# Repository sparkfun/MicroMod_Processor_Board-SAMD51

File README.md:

SparkFun MicroMod SAMD51 Processor
========================================

[*SparkFun MicroMod SAMD51 Processor (DEV-16791)*](https://www.sparkfun.com/products/16791)

With a 32-bit ARM Cortex-M4F MCU, the SparkFun MicroMod SAMD51 Processor Board is one powerful microcontroller packaged on a small board! The provides you with an economical and easy to use development platform if you're needing more power with minimal working space. This MicroMod SAMD51 even comes flashed with the same convenient UF2 bootloader like the SAMD51 Thing Plus and the RedBoard Turbo. The MicroMod SAMD51 uses the MicroMod Hardware pinout to easily switch between carrier boards.

The ATSAMD51J20 utilizes a 32-bit ARM Cortex-M4 processor with Floating Point Unit (FPU), running up to 120MHz, up to 1MB of flash memory, up to 256KB of SRAM with ECC, up to 6 SERCOM interfaces, and other features.

Repository Contents
-------------------

* **/Arduino Board Files** - Board definitions for MicroMod SAMD51
* **/Documentation** - Datasheets, additional product information
* **/Hardware** - Eagle design files (.brd, .sch)
* **/Production** - Production panel files (.brd)
* **/uf2-bootloader** - Default firmware

Documentation
--------------
* **[Graphical Datasheet](https://github.com/sparkfun/Graphical_Datasheets/tree/main/Datasheets/SAM51)** - Pinout of the SAMD51 Processor Board
* **[Installing Board Definitions in the Arduino IDE](https://learn.sparkfun.com/tutorials/installing-board-definitions-in-the-arduino-ide)** - Information about installing Arduino Board Files for Arduino
* **[Hookup Guide](https://learn.sparkfun.com/tutorials/micromod-samd51-processor-board-hookup-guide)** - Basic hookup guide

Product Versions
----------------
* [DEV-16791](https://www.sparkfun.com/products/16791)

Version History
---------------
* [v1.3](https://github.com/sparkfun/MicroMod_Processor_Board-SAMD51/tree/v1.3) - Minor update to swap SPI1 lines to the external flash
* [v1.2](https://github.com/sparkfun/MicroMod_Processor_Board-SAMD51/tree/v1.2) - Initial Release 

License Information
-------------------

This product is _**open source**_! 

Please review the LICENSE.md file for license information. 

If you have any questions or concerns on licensing, please contact technical support on our [SparkFun forums](https://forum.sparkfun.com/viewforum.php?f=152).

Distributed as-is; no warranty is given.

- Your friends at SparkFun.

_<COLLABORATION CREDIT>_

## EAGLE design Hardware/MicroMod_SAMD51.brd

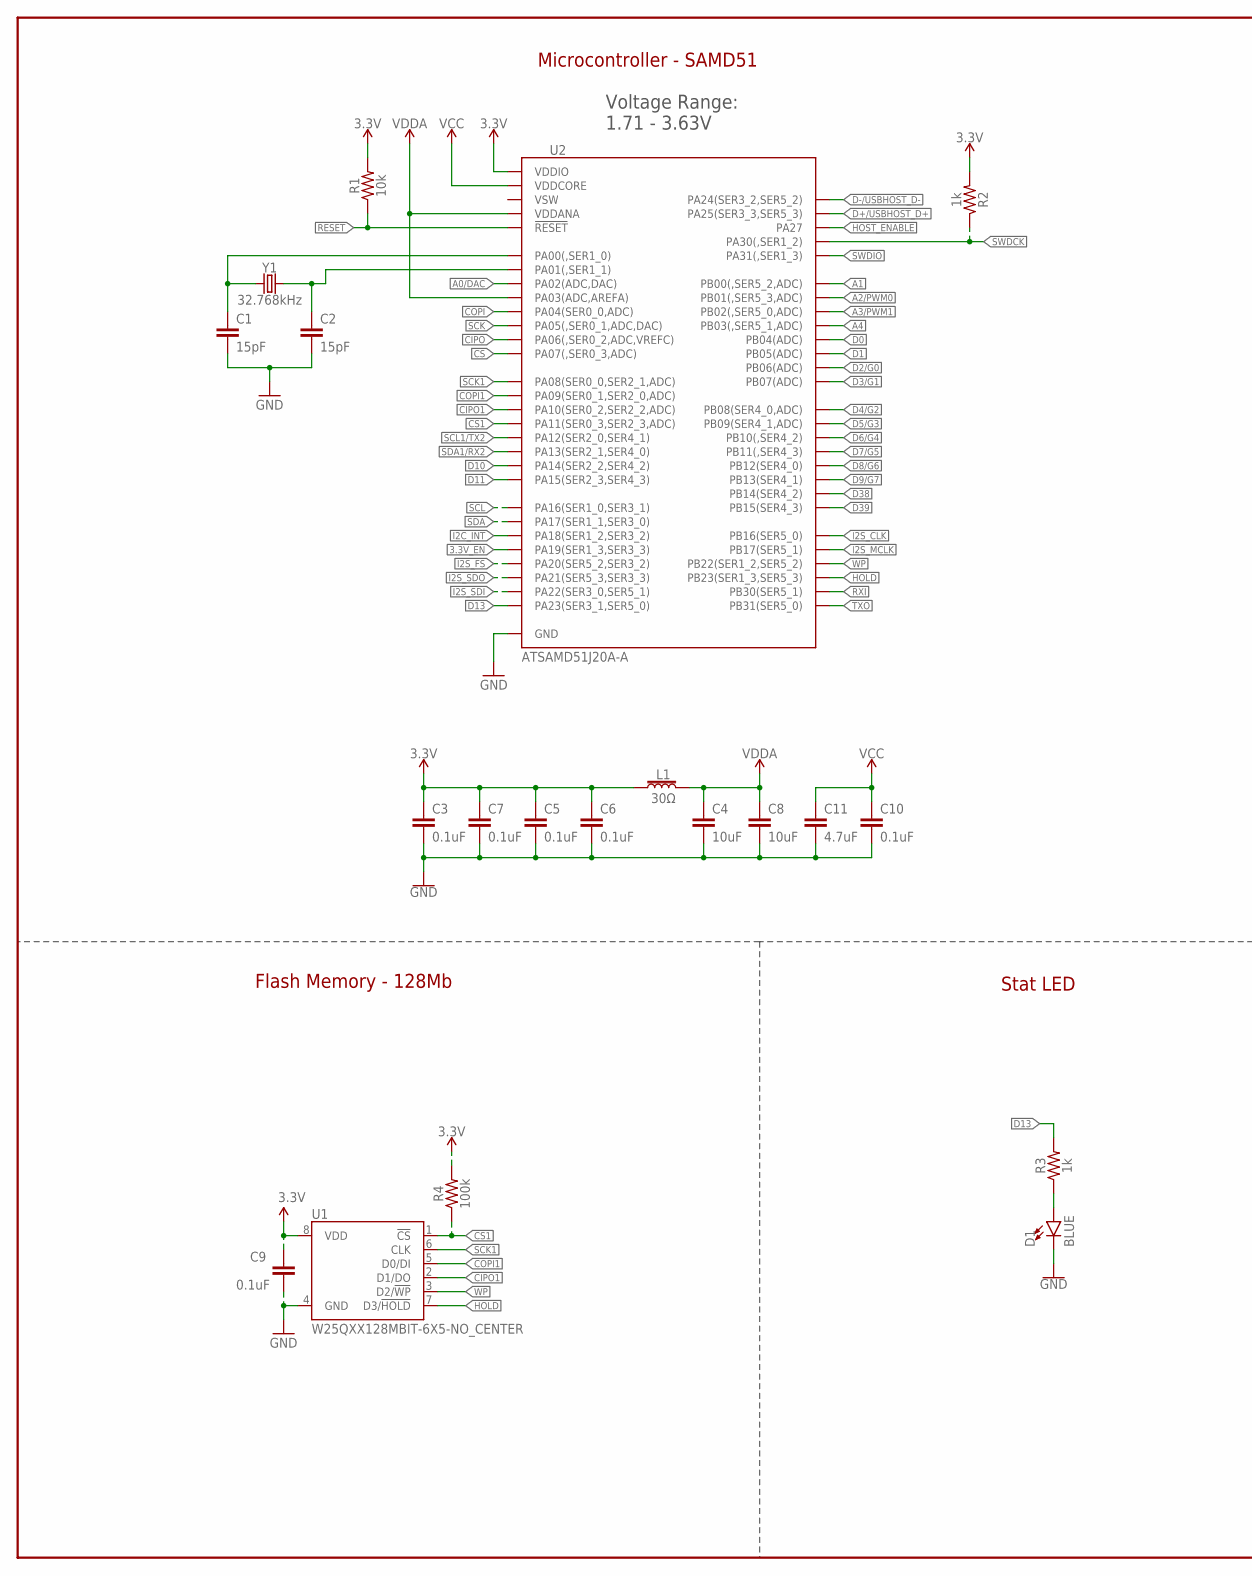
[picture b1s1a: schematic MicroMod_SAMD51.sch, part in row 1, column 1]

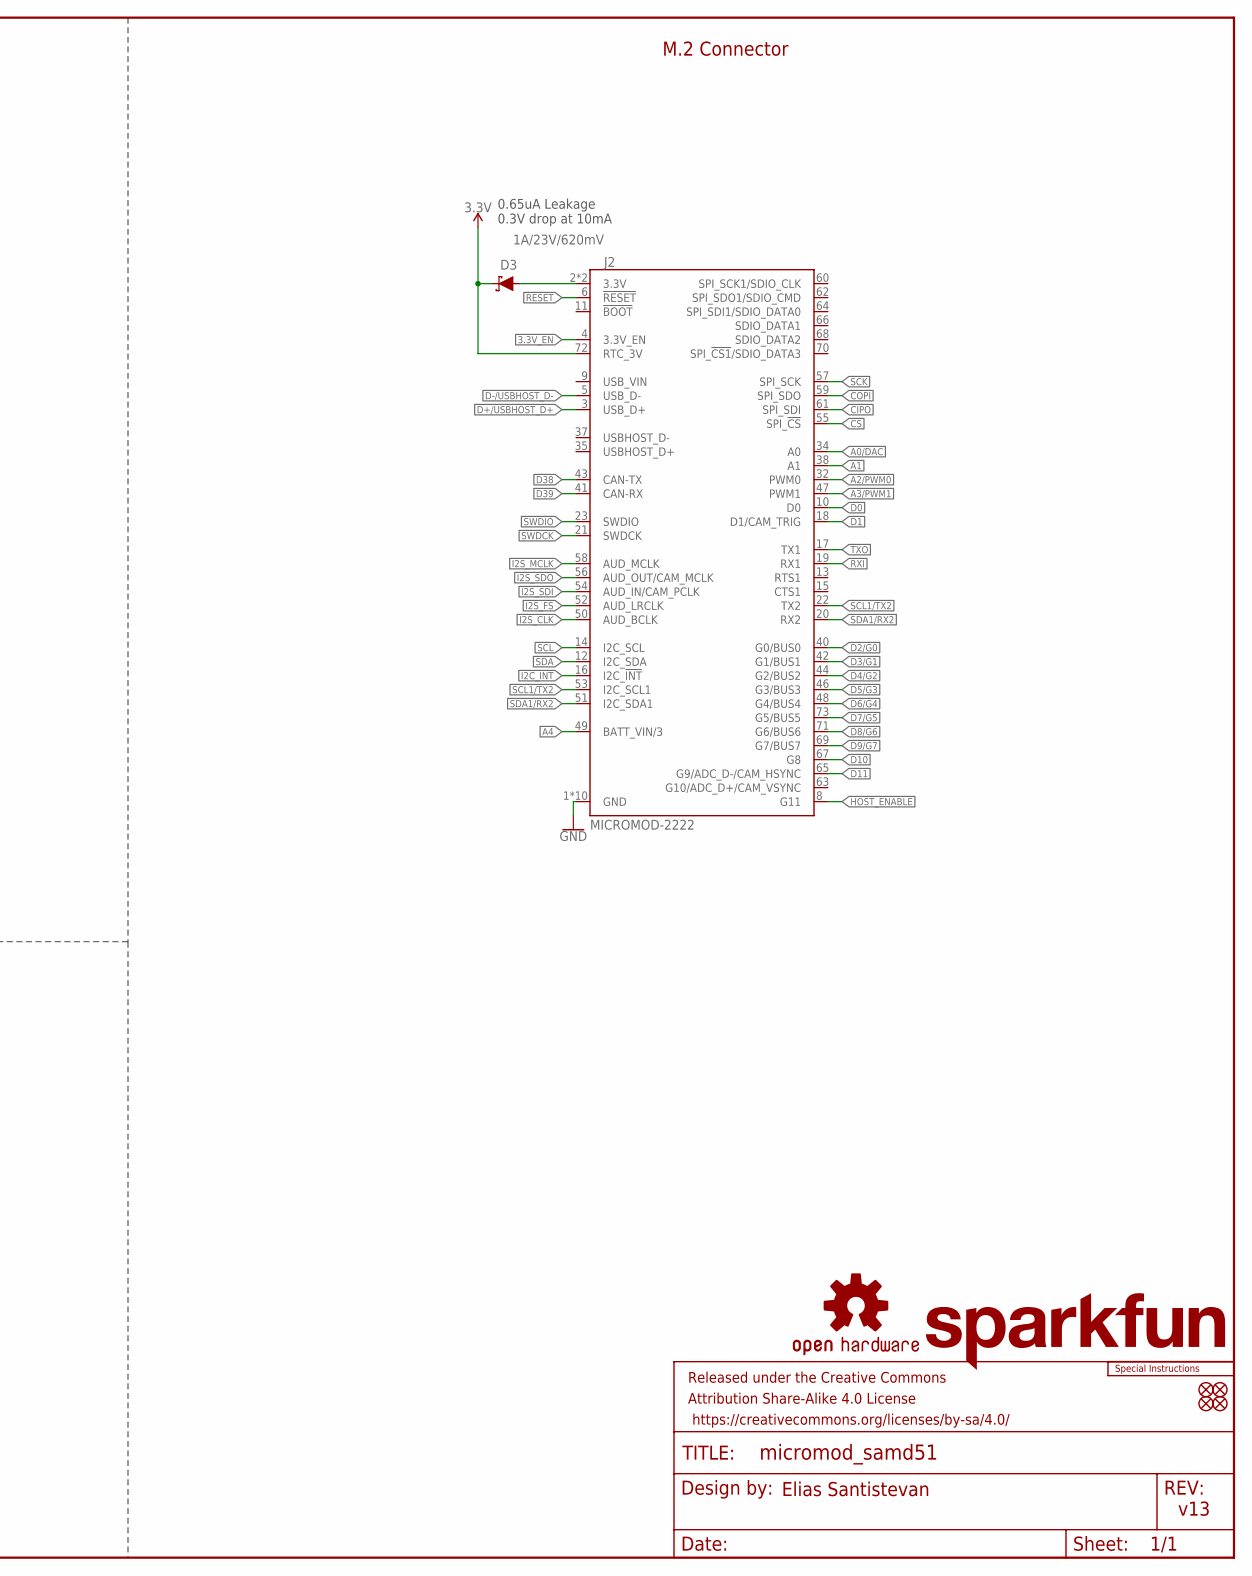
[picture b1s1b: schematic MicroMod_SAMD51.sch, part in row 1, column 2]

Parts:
C1, C2: 15pF; 0402-TIGHT
C3, C5, C6, C7, C9, C10: 0.1uF; 0402-TIGHT
C4, C8: 10uF; 0402-TIGHT
C11: 4.7uF; 0402-TIGHT
D1: BLUE; LED-0603
D3: 1A/23V/620mV; SOD-323
FD5, FD6, FD7, FD8: FIDUCIALUFIDUCIAL; FIDUCIAL-MICRO
FRAME2: FRAME-LEDGER; CREATIVE_COMMONS
J2: MICROMOD-2222; M.2-CARD-E-22
L1: 30Ω; 0402-TIGHT
LOGO2: OSHW-LOGOMINI; OSHW-LOGO-MINI
LOGO5: SPECIAL_INSTRUCTIONS-ORDERING; ORDERING_INSTRUCTIONS
LOGO6: SFE_LOGO_NAME.1_INCH; SFE_LOGO_NAME_.1
R1: 10k; 0402-TIGHT
R2, R3: 1k; 0402-TIGHT
R4: 100k; 0402-TIGHT
U1: W25QXX128MBIT-6X5-NO_CENTER; WSON-8-6X5-NO_CENTERPAD
U2: ATSAMD51J20A-A; TQFP64
Y1: 32.768kHz; CRYSTAL-SMD-3.2X1.5MM

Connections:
3.3V: C3.1, C5.1, C6.1, C7.1, C9.1, D3.C, J2.72 (RTC_3V), L1.1, R1.2, R2.2, R4.2, U1.8 (VDD), U2.21 (VDDIO), U2.34 (VDDIO), U2.48 (VDDIO), U2.56 (VDDIO)
3.3V_EN: J2.4 (3.3V_EN), U2.38 (PA19(SER1_3,SER3_3))
3.3V_IN: D3.A, J2.2 (3.3V), J2.74 (3.3V)
!CS: J2.55 (SPI_!CS!), U2.16 (PA07(,SER0_3,ADC))
!CS1!: R4.1, U1.1 (!CS!), U2.20 (PA11(SER0_3,SER2_3,ADC))
!HOLD!: U1.7 (D3/!HOLD!), U2.50 (PB23(SER1_3,SER5_3))
!RESET: J2.6 (!RESET!), R1.1, U2.52 (!RESET)
!WP!: U1.3 (D2/!WP!), U2.49 (PB22(SER1_2,SER5_2))
A0/DAC: J2.34 (A0), U2.3 (PA02(ADC,DAC))
A1: J2.38 (A1), U2.61 (PB00(,SER5_2,ADC))
A2/PWM0: J2.32 (PWM0), U2.62 (PB01(,SER5_3,ADC))
A3/PWM1: J2.47 (PWM1), U2.63 (PB02(,SER5_0,ADC))
A4: J2.49 (BATT_VIN/3), U2.64 (PB03(,SER5_1,ADC))
CIPO: J2.61 (SPI_SDI), U2.15 (PA06(,SER0_2,ADC,VREFC))
CIPO1: U1.2 (D1/DO), U2.19 (PA10(SER0_2,SER2_2,ADC))
COPI: J2.59 (SPI_SDO), U2.13 (PA04(SER0_0,ADC))
COPI1: U1.5 (D0/DI), U2.18 (PA09(SER0_1,SER2_0,ADC))
D0: J2.10 (D0), U2.5 (PB04(ADC))
D1: J2.18 (D1/CAM_TRIG), U2.6 (PB05(ADC))
D2/G0: J2.40 (G0/BUS0), U2.9 (PB06(ADC))
D3/G1: J2.42 (G1/BUS1), U2.10 (PB07(ADC))
D4/G2: J2.44 (G2/BUS2), U2.11 (PB08(SER4_0,ADC))
D5/G3: J2.46 (G3/BUS3), U2.12 (PB09(SER4_1,ADC))
D6/G4: J2.48 (G4/BUS4), U2.23 (PB10(,SER4_2))
D7/G5: J2.73 (G5/BUS5), U2.24 (PB11(,SER4_3))
D8/G6: J2.71 (G6/BUS6), U2.25 (PB12(SER4_0))
D9/G7: J2.69 (G7/BUS7), U2.26 (PB13(SER4_1))
D10: J2.67 (G8), U2.31 (PA14(SER2_2,SER4_2))
D11: J2.65 (G9/ADC_D-/CAM_HSYNC), U2.32 (PA15(SER2_3,SER4_3))
D13: R3.2, U2.44 (PA23(SER3_1,SER5_0))
D38: J2.43 (CAN-TX), U2.27 (PB14(SER4_2))
D39: J2.41 (CAN-RX), U2.28 (PB15(SER4_3))
D+/USBHOST_D+: J2.3 (USB_D+), U2.46 (PA25(SER3_3,SER5_3))
D-/USBHOST_D-: J2.5 (USB_D-), U2.45 (PA24(SER3_2,SER5_2))
GND: C1.2, C2.2, C3.2, C4.2, C5.2, C6.2, C7.2, C8.2, C9.2, C10.2, C11.2, D1.C, J2.1 (GND), J2.7 (GND), J2.33 (GND), J2.36 (GND), J2.39 (GND), J2.45 (GND), J2.75 (GND), J2.GND1 (GND), J2.GND2 (GND), J2.GND3 (GND), U1.4 (GND), U2.7 (GND), U2.22 (GND), U2.33 (GND), U2.47 (GND), U2.54 (GND)
HOST_ENABLE: J2.8 (G11), U2.51 (PA27)
I2C_!INT!: J2.16 (I2C_!INT!), U2.37 (PA18(SER1_2,SER3_2))
I2S_CLK: J2.50 (AUD_BCLK), U2.39 (PB16(SER5_0))
I2S_FS: J2.52 (AUD_LRCLK), U2.41 (PA20(SER5_2,SER3_2))
I2S_MCLK: J2.58 (AUD_MCLK), U2.40 (PB17(SER5_1))
I2S_SDI: J2.54 (AUD_IN/CAM_PCLK), U2.43 (PA22(SER3_0,SER5_1))
I2S_SDO: J2.56 (AUD_OUT/CAM_MCLK), U2.42 (PA21(SER5_3,SER3_3))
unnamed: D1.A, R3.1
RXI: J2.19 (RX1), U2.59 (PB30(SER5_1))
SCK: J2.57 (SPI_SCK), U2.14 (PA05(,SER0_1,ADC,DAC))
SCK1: U1.6 (CLK), U2.17 (PA08(SER0_0,SER2_1,ADC))
SCL: J2.14 (I2C_SCL), U2.35 (PA16(SER1_0,SER3_1))
SCL1/TX2: J2.22 (TX2), J2.53 (I2C_SCL1), U2.29 (PA12(SER2_0,SER4_1))
SDA: J2.12 (I2C_SDA), U2.36 (PA17(SER1_1,SER3_0))
SDA1/RX2: J2.20 (RX2), J2.51 (I2C_SDA1), U2.30 (PA13(SER2_1,SER4_0))
SWDCK: J2.21 (SWDCK), R2.1, U2.57 (PA30(,SER1_2))
SWDIO: J2.23 (SWDIO), U2.58 (PA31(,SER1_3))
TXO: J2.17 (TX1), U2.60 (PB31(SER5_0))
VCC: C10.1, C11.1, U2.53 (VDDCORE)
VDDA: C4.1, C8.1, L1.2, U2.4 (PA03(ADC,AREFA)), U2.8 (VDDANA)
XIN32: C1.1, U2.1 (PA00(,SER1_0)), Y1.P$1 (1)
XOUT32: C2.1, U2.2 (PA01(,SER1_1)), Y1.P$2 (2)

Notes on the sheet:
v13
M.2 Connector
Microcontroller - SAMD51
Flash Memory - 128Mb
Stat LED
Elias Santistevan
0.65uA Leakage 0.3V drop at 10mA
Voltage Range: 1.71 - 3.63V

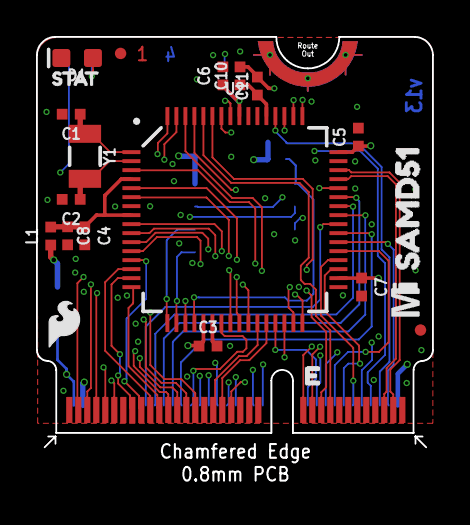
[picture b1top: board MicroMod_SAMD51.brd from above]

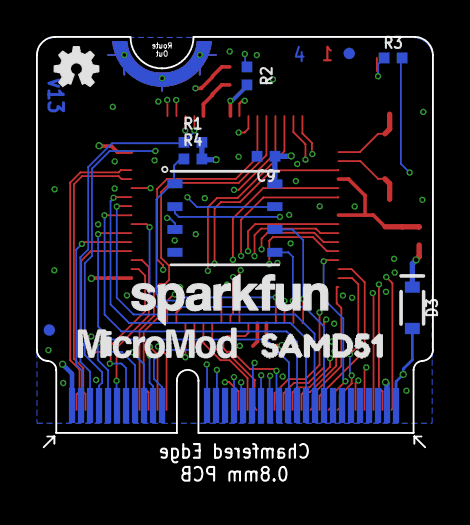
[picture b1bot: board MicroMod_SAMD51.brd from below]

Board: 4 copper layers, 22.0 x 22.8 mm, 36 parts (13 on the bottom side), 57 nets.

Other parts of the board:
U$1: MICROMOD_MI_LOGO_.35
U$4: MICROMOD_LOGO_.35
U$5, U$6: SAMD510
U$7: SFE_LOGO_FLAME_.1
U$8: STAT0

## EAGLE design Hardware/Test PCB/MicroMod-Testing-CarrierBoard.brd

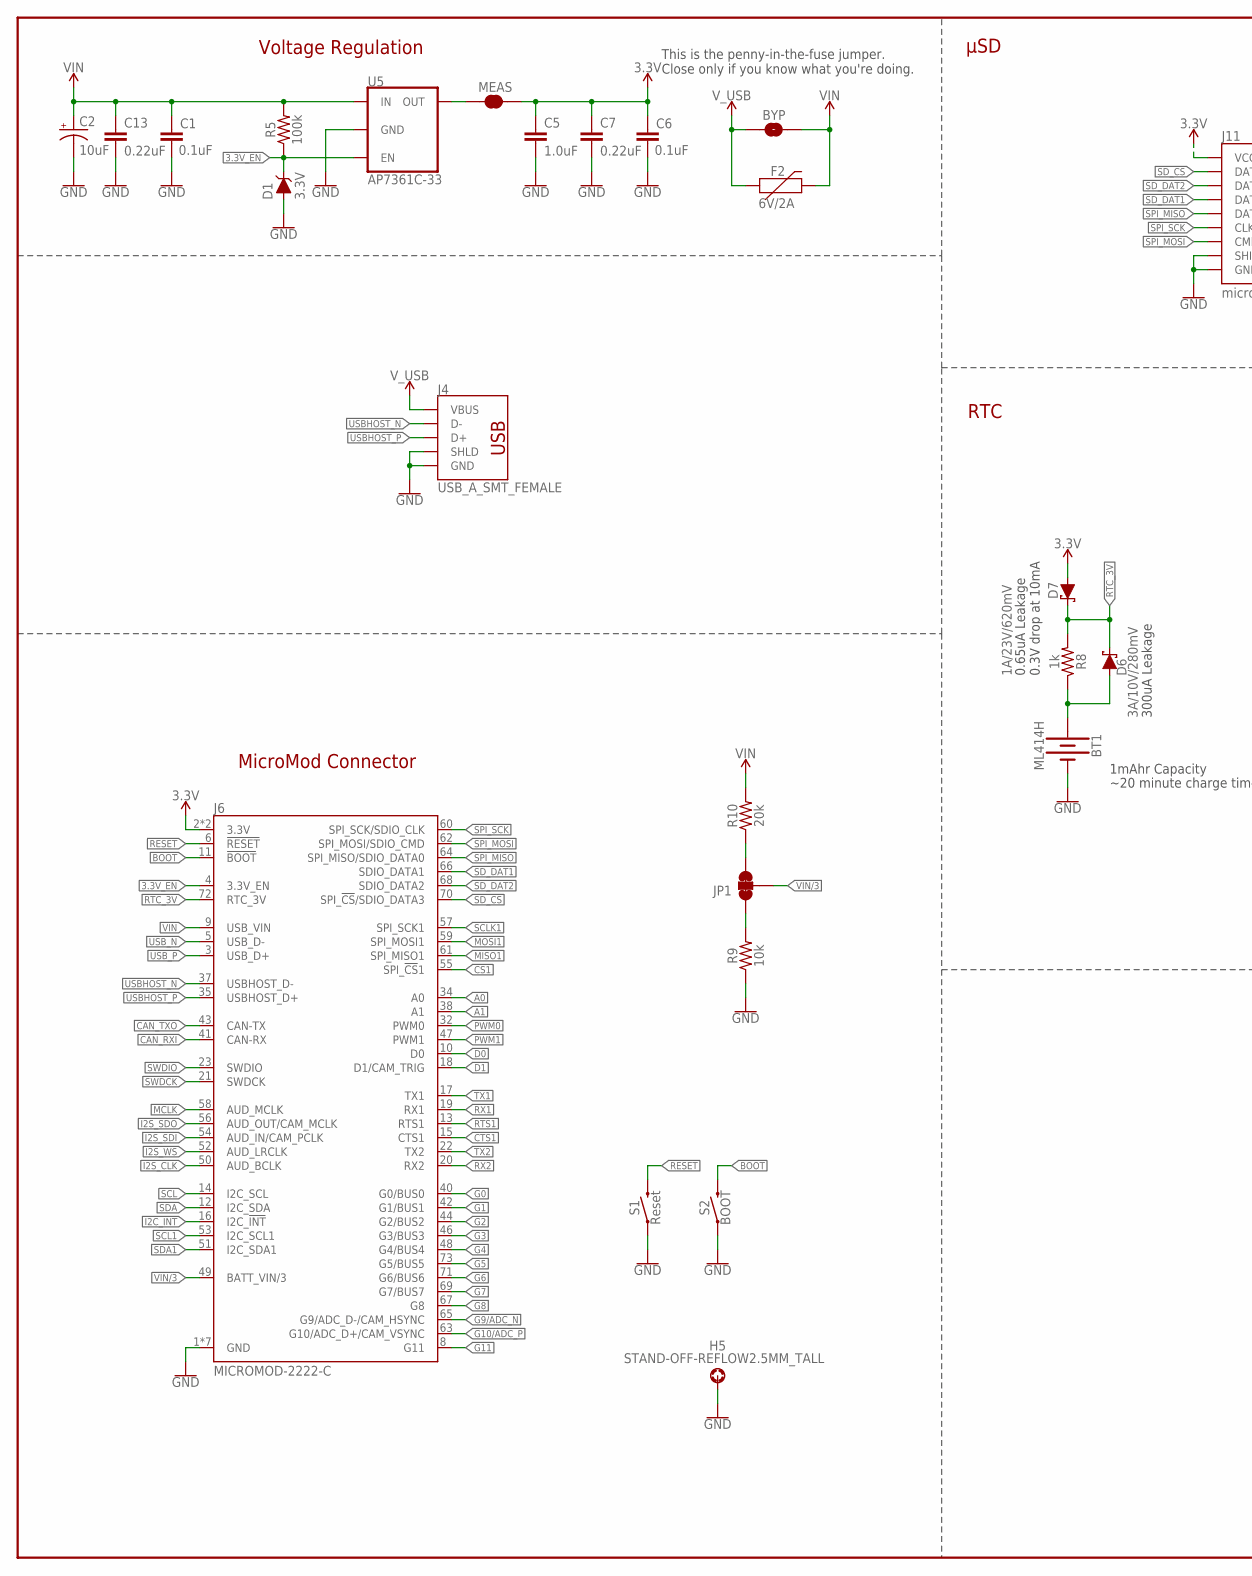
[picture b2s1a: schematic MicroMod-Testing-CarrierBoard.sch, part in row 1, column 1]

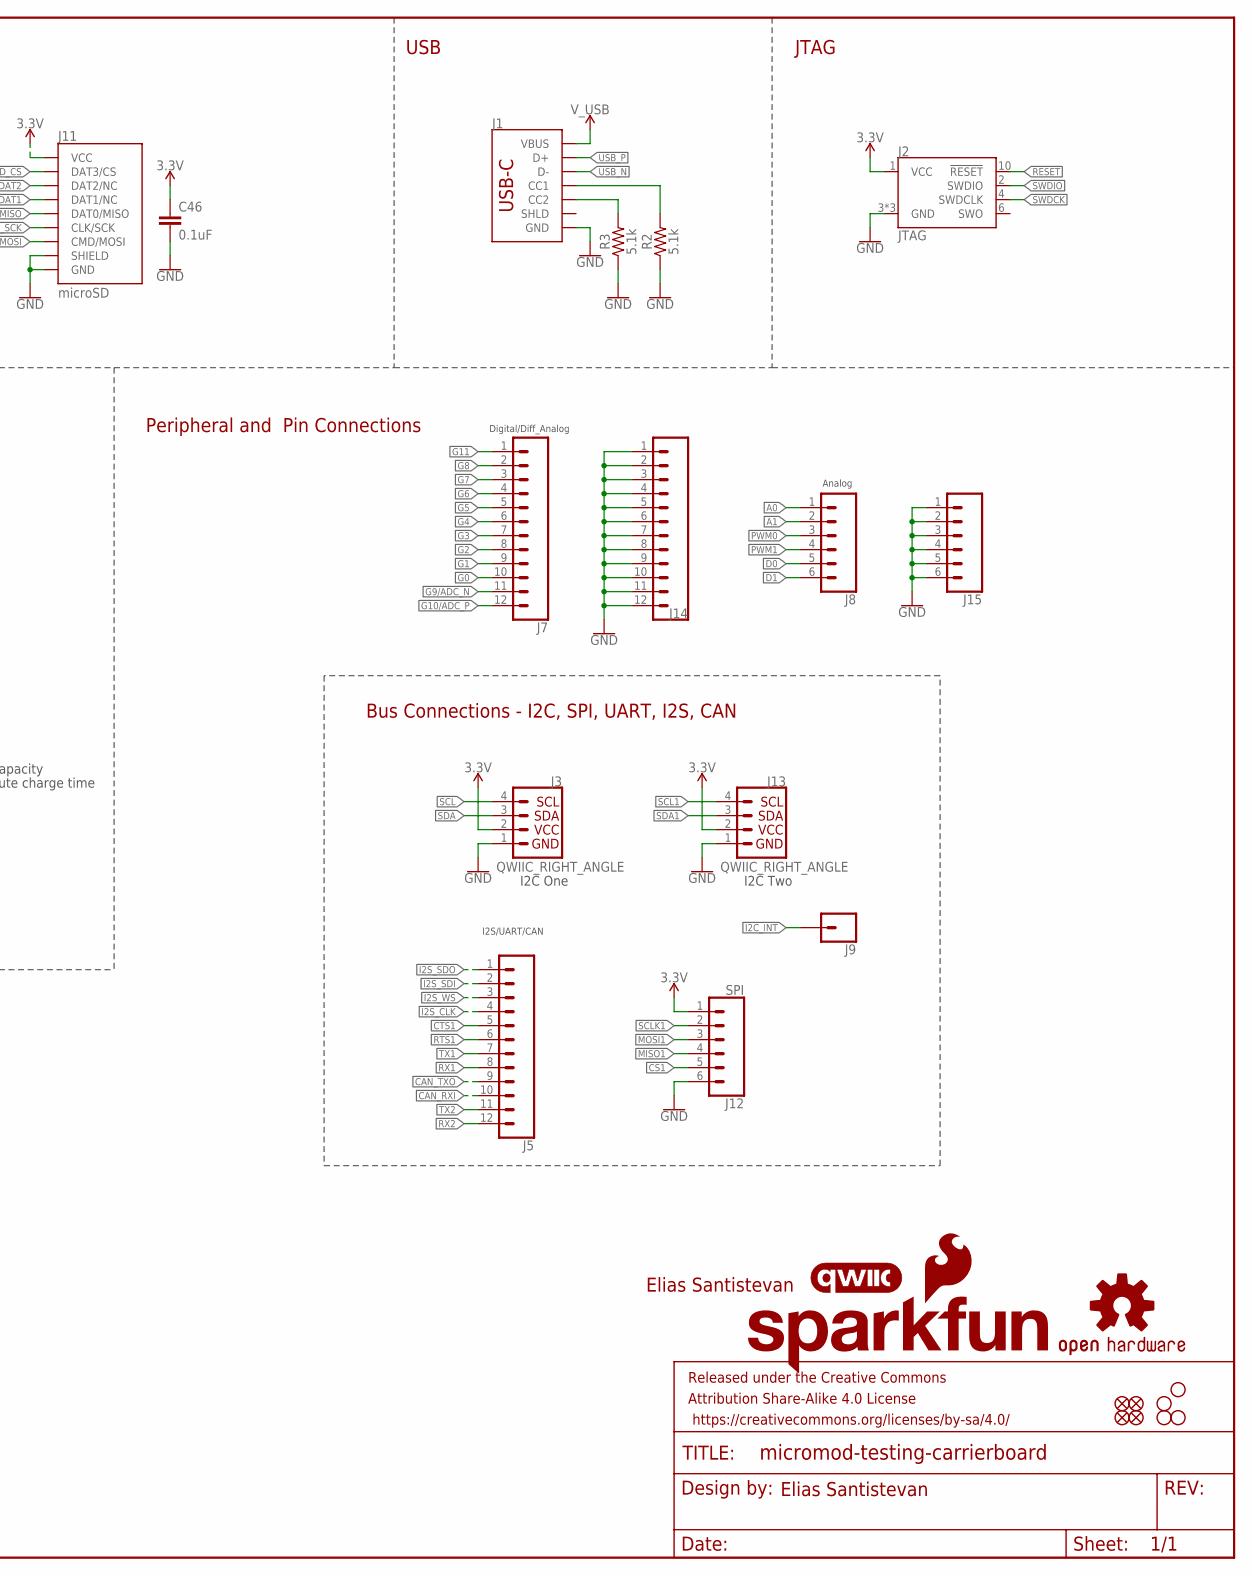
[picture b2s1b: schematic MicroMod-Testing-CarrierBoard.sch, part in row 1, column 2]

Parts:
BT1: ML414H; ML414H_IV01E
BYP: JUMPER-SMT_2_NO_SILK; SMT-JUMPER_2_NO_SILK
C1, C6, C46: 0.1uF; 0603
C2: 10uF; EIA3216
C5: 1.0uF; 0603
C7, C13: 0.22uF; 0603
D1: 3.3V; SOD-323
D6: 3A/10V/280mV; SOD-323
D7: 1A/23V/620mV; SOD-323
F2: 6V/2A; 1210
FD1, FD2, FD3, FD4: FIDUCIALUFIDUCIAL; FIDUCIAL-MICRO
FRAME1: FRAME-LEDGER; CREATIVE_COMMONS
H1, H2, H3, H4: STAND-OFF
H5: STAND-OFF-REFLOW2.5MM_TALL; STAND-OFF-REFLOW-M2.5
J1: USB_C_2-LAYER_PADS; USB-C-16P-2LAYER-PADS
J2: JTAG; 2X5-PTH-1.27MM
J3, J13: QWIIC_RIGHT_ANGLE; JST04_1MM_RA
J4: USB_A_SMT_FEMALE; USB-A-S-SILK-FEMALE
J5, J7, J14: CONN_12NO_SILK; 1X12_NO_SILK
J6: MICROMOD-2222-C; M.2-CONNECTOR-E
J8, J15: Dedicated; 1X06_NO_SILK
J9: CONN_01PTH_NO_SILK_YES_STOP; 1X01_NO_SILK
J11: microSD; MICRO-SD-SOCKET
J12: SPI; 1X06_NO_SILK
JP1: JUMPER-SMT_3_2-NC_TRACE_SILK; SMT-JUMPER_3_2-NC_TRACE_SILK
LOGO1: SFE_LOGO_NAME_FLAME.1_INCH; SFE_LOGO_NAME_FLAME_.1
LOGO2: QWIIC_LOGO_CONNECTOR; QWIIC_5.5MM
LOGO3: OSHW-LOGOMINI; OSHW-LOGO-MINI
MEAS: JUMPER-COMBO_2_NC_TRACE; COMBO-JUMPER_2_NC_TRACE
R2, R3: 5.1k; 0603
R5: 100k; 0603
R8: 1k; 0603
R9: 10k; 0603
R10: 20k; 0603
S1: Reset; TACTILE_SWITCH_SMD_5.2MM
S2: BOOT; TACTILE_SWITCH_SMD_5.2MM
U5: AP7361C-33; UDFN-8

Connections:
3.3V: C5.1, C6.1, C7.1, C46.1, D7.A, J2.1 (VCC), J3.2, J6.2 (3.3V), J6.74 (3.3V), J11.VCC, J12.1, J13.2, MEAS.2, MEAS.4 (2)
3.3V_EN: D1.C, J6.4 (3.3V_EN), R5.1, U5.5 (EN)
!BOOT!: J6.11 (!BOOT!), S2.3 (2), S2.4 (2)
!CS1: J6.55 (SPI_!CS!1), J12.5
!RESET!: J2.10 (!RESET), J6.6 (!RESET!), S1.3 (2), S1.4 (2)
A0: J6.34 (A0), J8.1
A1: J6.38 (A1), J8.2
CAN_RXI: J5.10, J6.41 (CAN-RX)
CAN_TXO: J5.9, J6.43 (CAN-TX)
CTS1: J5.5, J6.15 (CTS1)
D0: J6.10 (D0), J8.5
D1: J6.18 (D1/CAM_TRIG), J8.6
G0: J6.40 (G0/BUS0), J7.10
G1: J6.42 (G1/BUS1), J7.9
G2: J6.44 (G2/BUS2), J7.8
G3: J6.46 (G3/BUS3), J7.7
G4: J6.48 (G4/BUS4), J7.6
G5: J6.73 (G5/BUS5), J7.5
G6: J6.71 (G6/BUS6), J7.4
G7: J6.69 (G7/BUS7), J7.3
G8: J6.67 (G8), J7.2
G9/ADC_N: J6.65 (G9/ADC_D-/CAM_HSYNC), J7.11
G10/ADC_P: J6.63 (G10/ADC_D+/CAM_VSYNC), J7.12
G11: J6.8 (G11), J7.1
GND: BT1.-, C1.2, C2.-, C5.2, C6.2, C7.2, C13.2, C46.2, D1.A, H5.1, J1.GND, J1.GND2 (GND), J2.3 (GND), J2.5 (GND), J2.9 (GND), J3.1, J4.GND, J4.SHLD1 (SHLD), J4.SHLD2 (SHLD), J6.1 (GND), J6.7 (GND), J6.33 (GND), J6.36 (GND), J6.39 (GND), J6.45 (GND), J6.75 (GND), J11.CD1 (SHIELD), J11.GND, J11.GND1 (GND), J11.GND3 (GND), J12.6, J13.1, J14.1, J14.2, J14.3, J14.4, J14.5, J14.6, J14.7, J14.8, J14.9, J14.10, J14.11, J14.12, J15.1, J15.2, J15.3, J15.4, J15.5, J15.6, R2.1, R3.1, R9.1, S1.1, S1.2 (1), S2.1, S2.2 (1), U5.4 (GND), U5.EP (GND)
I2C_!INT: J6.16 (I2C_!INT!), J9.1
I2S_CLK: J5.4, J6.50 (AUD_BCLK)
I2S_SDI: J5.2, J6.54 (AUD_IN/CAM_PCLK)
I2S_SDO: J5.1, J6.56 (AUD_OUT/CAM_MCLK)
I2S_WS: J5.3, J6.52 (AUD_LRCLK)
MCLK: J6.58 (AUD_MCLK)
MISO1: J6.61 (SPI_MISO1), J12.4
MOSI1: J6.59 (SPI_MOSI1), J12.3
unnamed: JP1.3, R10.1
unnamed: JP1.1, R9.2
unnamed: J1.A5 (CC1), R2.2
unnamed: J1.B5 (CC2), R3.2
unnamed: BT1.+, D6.A, R8.1
OUT_MEAS: MEAS.1, MEAS.3 (1), U5.1 (OUT)
PWM0: J6.32 (PWM0), J8.3
PWM1: J6.47 (PWM1), J8.4
RTC_3V: D6.C, D7.C, J6.72 (RTC_3V), R8.2
RTS1: J5.6, J6.13 (RTS1)
RX1: J5.8, J6.19 (RX1)
RX2: J5.12, J6.20 (RX2)
SCL: J3.4, J6.14 (I2C_SCL)
SCL1: J6.53 (I2C_SCL1), J13.4
SCLK1: J6.57 (SPI_SCK1), J12.2
SDA: J3.3, J6.12 (I2C_SDA)
SDA1: J6.51 (I2C_SDA1), J13.3
SD_!CS!: J6.70 (SPI_!CS!/SDIO_DATA3), J11.CS (DAT3/CS)
SD_DAT1: J6.66 (SDIO_DATA1), J11.RSV2 (DAT1/NC)
SD_DAT2: J6.68 (SDIO_DATA2), J11.RSV1 (DAT2/NC)
SPI_MISO: J6.64 (SPI_MISO/SDIO_DATA0), J11.DO (DAT0/MISO)
SPI_MOSI: J6.62 (SPI_MOSI/SDIO_CMD), J11.DI (CMD/MOSI)
SPI_SCK: J6.60 (SPI_SCK/SDIO_CLK), J11.SCLK (CLK/SCK)
SWDCK: J2.4 (SWDCLK), J6.21 (SWDCK)
SWDIO: J2.2 (SWDIO), J6.23 (SWDIO)
TX1: J5.7, J6.17 (TX1)
TX2: J5.11, J6.22 (TX2)
USBHOST_N: J4.D-, J6.37 (USBHOST_D-)
USBHOST_P: J4.D+, J6.35 (USBHOST_D+)
USB_N: J1.A7 (D-), J1.B7 (D-), J6.5 (USB_D-)
USB_P: J1.A6 (D+), J1.B6 (D+), J6.3 (USB_D+)
VIN: BYP.2, C1.1, C2.+, C13.1, F2.2, J6.9 (USB_VIN), R5.2, R10.2, U5.8 (IN)
VIN/3: J6.49 (BATT_VIN/3), JP1.2
V_USB: BYP.1, F2.1, J1.VBUS1 (VBUS), J1.VBUS2 (VBUS), J4.VBUS

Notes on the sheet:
μSD
300uA Leakage
0.65uA Leakage 0.3V drop at 10mA
~20 minute charge time
1mAhr Capacity
This is the penny-in-the-fuse jumper. Close only if you know what you're doing.
JTAG
USB
Peripheral and Pin Connections
RTC
Voltage Regulation
MicroMod Connector
I2C One
I2C Two
Analog
Bus Connections - I2C, SPI, UART, I2S, CAN
Elias Santistevan
I2S/UART/CAN
Digital/Diff_Analog

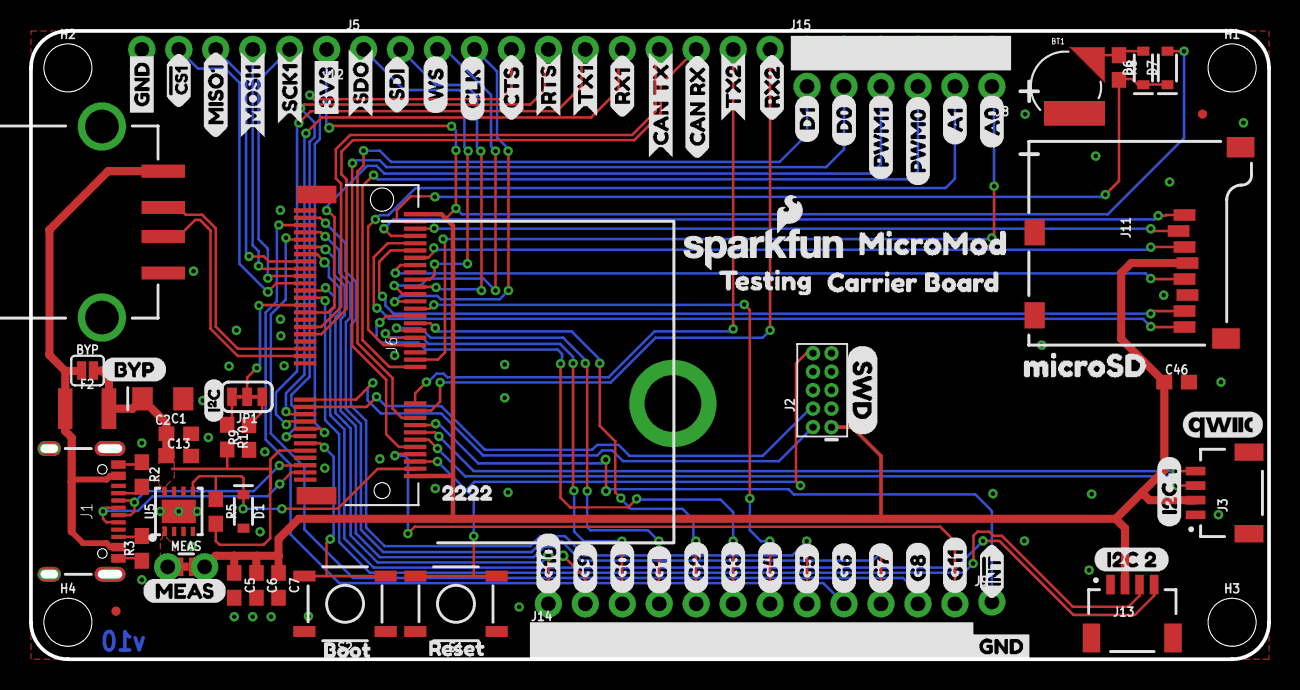
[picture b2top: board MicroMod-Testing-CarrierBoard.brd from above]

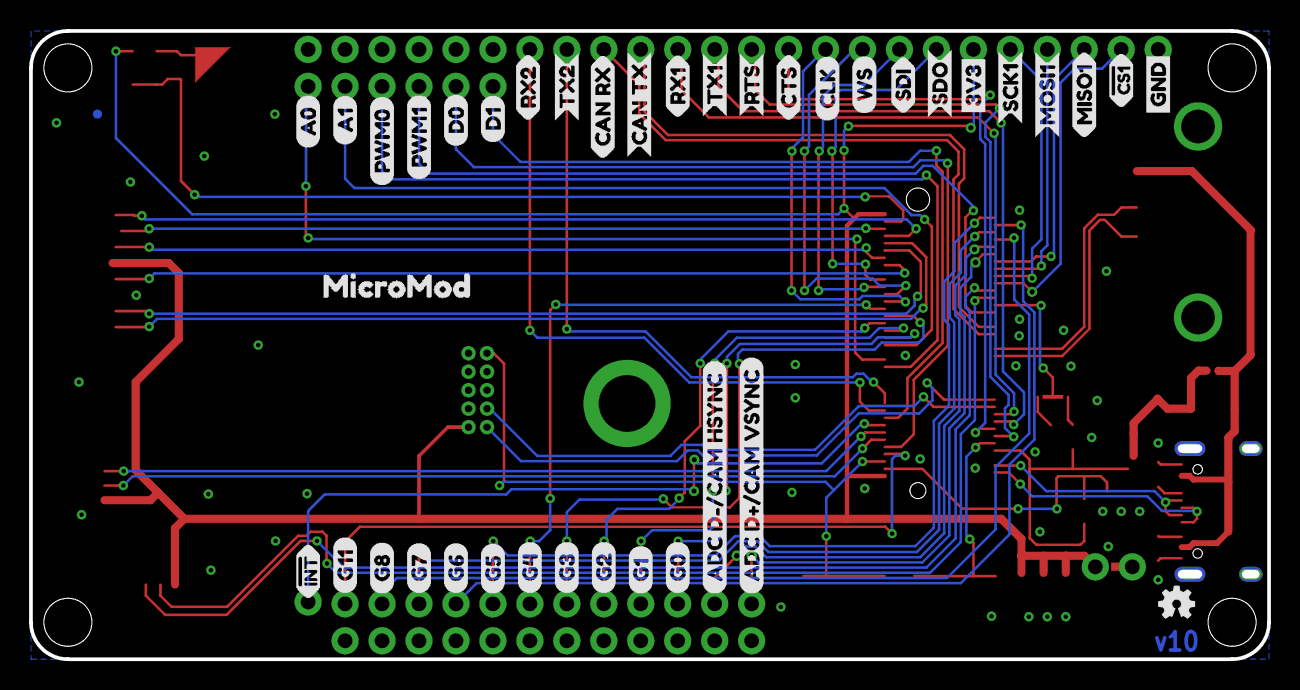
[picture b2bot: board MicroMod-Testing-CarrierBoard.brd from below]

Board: 2 copper layers, 85.1 x 43.2 mm, 140 parts (41 on the bottom side), 66 nets.

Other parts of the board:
U$1, U$89: G00
U$2: RESET3
U$3, U$88: G11
U$4, U$87: G22
U$5: MEAS
U$6, U$53, U$73: GND_P
U$7: ADC_D##CAM_HSYNC0
U$8: ADC_D##CAM_VSYNC1
U$9, U$74: #CS13
U$10, U$75: MISO10
U$11, U$86: G33
U$12, U$13: D13
U$14, U$16: D02
U$15, U$61: PWM10
U$17, U$85: G44
U$18, U$84: G55
U$19: BOOT2
U$20, U$83: G66
U$21, U$35: !INT_I
U$22, U$82: G77
U$23, U$26: 3V3_P
U$24, U$64: MICROMOD0
U$25, U$29: RX10
U$27: BYP
U$28: MICROSD4
U$30, U$80: G118
U$31, U$41: TX13
U$32, U$81: G811
U$33: G1010
U$34, U$48: CAN_RX2
U$36, U$54: CAN_TX3
U$37, U$62: CLK3
U$38, U$63: SDI1
U$39, U$65: SDO0
U$40, U$66: WS2
U$42: I2C_32
U$43, U$44: A00
U$45: CARRIER_BOARD0
U$46: TESTING0
U$47: SWD0
U$49, U$76: MOSI11
U$50, U$77: SCK12
U$51, U$78: CTS0
U$52, U$79: RTS1
U$55: 22229
U$56: G90
U$57, U$58: A10
U$59, U$60: PWM01
U$67: I2C_10
U$68: I2C_21
U$69, U$70: RX23
U$71, U$72: TX22

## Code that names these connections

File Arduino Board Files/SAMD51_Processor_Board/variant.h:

/*
  Copyright (c) 2014-2015 Arduino LLC.  All right reserved.

  This library is free software; you can redistribute it and/or
  modify it under the terms of the GNU Lesser General Public
  License as published by the Free Software Foundation; either
  version 2.1 of the License, or (at your option) any later version.

  This library is distributed in the hope that it will be useful,
  but WITHOUT ANY WARRANTY; without even the implied warranty of
  MERCHANTABILITY or FITNESS FOR A PARTICULAR PURPOSE.
  See the GNU Lesser General Public License for more details.

  You should have received a copy of the GNU Lesser General Public
  License along with this library; if not, write to the Free Software
  Foundation, Inc., 51 Franklin St, Fifth Floor, Boston, MA  02110-1301  USA
*/

#ifndef _VARIANT_SAMD51_MICROMOD_
#define _VARIANT_SAMD51_MICROMOD_

// The definitions here needs a SAMD core >=1.6.10
#define ARDUINO_SAMD_VARIANT_COMPLIANCE 10610

//----------------------------------------------------------------------------
//        Definitions
//----------------------------------------------------------------------------

/** Frequency of the board main oscillator */
#define VARIANT_MAINOSC		(32768ul)

/** Master clock frequency */
#define VARIANT_MCK			  (120000000ul)

#define VARIANT_GCLK0_FREQ (120000000UL)
#define VARIANT_GCLK1_FREQ (48000000UL)
#define VARIANT_GCLK2_FREQ (100000000UL)

//----------------------------------------------------------------------------
//        Headers
//----------------------------------------------------------------------------

#include "WVariant.h"

#ifdef __cplusplus
#include "SERCOM.h"
#include "Uart.h"
#endif // __cplusplus

#ifdef __cplusplus
extern "C"
{
#endif // __cplusplus

//----------------------------------------------------------------------------
//        Pins
//----------------------------------------------------------------------------

// Number of pins defined in PinDescription array
#define PINS_COUNT           (53u)
#define NUM_DIGITAL_PINS     (16u)
#define NUM_ANALOG_INPUTS    (11u)
#define NUM_ANALOG_OUTPUTS   (1u)
#define analogInputToDigitalPin(p)  ((p < 6u) ? (p) + 14u : -1)

#define digitalPinToPort(P)        ( &(PORT->Group[g_APinDescription[P].ulPort]) )
#define digitalPinToBitMask(P)     ( 1 << g_APinDescription[P].ulPin )
//#define analogInPinToBit(P)        ( )
#define portOutputRegister(port)   ( &(port->OUT.reg) )
#define portInputRegister(port)    ( &(port->IN.reg) )
#define portModeRegister(port)     ( &(port->DIR.reg) )
#define digitalPinHasPWM(P)        ( g_APinDescription[P].ulPWMChannel != NOT_ON_PWM || g_APinDescription[P].ulTCChannel != NOT_ON_TIMER )

/*
 * digitalPinToTimer(..) is AVR-specific and is not defined for SAMD
 * architecture. If you need to check if a pin supports PWM you must
 * use digitalPinHasPWM(..).
 *
 * https://github.com/arduino/Arduino/issues/1833
 */
// #define digitalPinToTimer(P)

// LEDs
//-------------------------------------------
#define PIN_LED_13           (13u)
#define PIN_LED              PIN_LED_13
#define LED_BUILTIN          PIN_LED_13
//-------------------------------------------

// Analog pins
//-------------------------------------------
#define PIN_A0               (17ul)
#define PIN_A1               (PIN_A0 + 1)
#define PIN_A2               (PIN_A0 + 2)
#define PIN_A3               (PIN_A0 + 4)
#define PIN_A4               (PIN_A0 + 5)
#define PIN_A5               (PIN_A0 + 6)
#define PIN_A6               (PIN_A0 + 7)

//DAC
#define PIN_DAC0             PIN_A0

static const uint8_t A0   = PIN_A0;
static const uint8_t A1   = PIN_A1;
static const uint8_t A2   = PIN_A2;
static const uint8_t A3   = PIN_A3;
static const uint8_t A4   = PIN_A4;
static const uint8_t A5   = PIN_A5;
static const uint8_t A6   = PIN_A6;
static const uint8_t A7   = PIN_A7;
static const uint8_t A8   = PIN_A8;
static const uint8_t A9   = PIN_A9;
static const uint8_t A10  = PIN_A10;

static const uint8_t DAC0 = PIN_DAC0;

#define ADC_RESOLUTION		12
//-------------------------------------------

// Other pins
//-------------------------------------------
#define PIN_ATN              (53ul)
static const uint8_t ATN = PIN_ATN;
//-------------------------------------------

// Serial1 
//-------------------------------------------
#define PIN_SERIAL1_RX       (32ul)
#define PIN_SERIAL1_TX       (33ul)
#define PAD_SERIAL1_TX       (UART_TX_PAD_0)
#define PAD_SERIAL1_RX       (SERCOM_RX_PAD_1)
//-------------------------------------------

// SPI Interfaces
//-------------------------------------------
#define SPI_INTERFACES_COUNT 1
  
#define PIN_SPI_MOSI         (45u)
#define PIN_SPI_SCK          (46u)
#define PIN_SPI_MISO         (47u)
#define PIN_SPI_SS           (48u)
#define PERIPH_SPI           sercom0
#define PAD_SPI_TX           SPI_PAD_0_SCK_1
#define PAD_SPI_RX           SERCOM_RX_PAD_2

static const uint8_t SS	  = PIN_SPI_SS ;
static const uint8_t MOSI = PIN_SPI_MOSI ;
static const uint8_t MISO = PIN_SPI_MISO ;
static const uint8_t SCK  = PIN_SPI_SCK ;  

// SPI1
#define PIN_SPI1_MOSI         (49u)
#define PIN_SPI1_SCK          (50u)
#define PIN_SPI1_MISO         (51u)
#define PIN_SPI1_SS           (52u)
#define PERIPH_SPI1           sercom5
#define PAD_SPI1_TX           SPI_PAD_0_SCK_1
#define PAD_SPI1_RX           SERCOM_RX_PAD_2
//-------------------------------------------

static const uint8_t SS1	 = PIN_SPI1_SS ; 	
static const uint8_t MOSI1 = PIN_SPI1_MOSI ;
static const uint8_t MISO1 = PIN_SPI1_MISO ;
static const uint8_t SCK1  = PIN_SPI1_SCK ;

// Wire Interfaces
//-------------------------------------------
#define WIRE_INTERFACES_COUNT 1

#define PIN_WIRE_SCL         (34u)
#define PIN_WIRE_SDA         (35u)
#define PERIPH_WIRE          sercom3
#define WIRE_IT_HANDLER      SERCOM3_Handler
#define WIRE_IT_HANDLER_0    SERCOM3_0_Handler
#define WIRE_IT_HANDLER_1    SERCOM3_1_Handler
#define WIRE_IT_HANDLER_2    SERCOM3_2_Handler
#define WIRE_IT_HANDLER_3    SERCOM3_3_Handler

static const uint8_t SDA = PIN_WIRE_SDA;
static const uint8_t SCL = PIN_WIRE_SCL;

#define PIN_WIRE1_SCL         (36u)
#define PIN_WIRE1_SDA         (37u)
#define PERIPH_WIRE1          sercom4
#define WIRE1_IT_HANDLER      SERCOM4_Handler
#define WIRE1_IT_HANDLER_0    SERCOM4_0_Handler
#define WIRE1_IT_HANDLER_1    SERCOM4_1_Handler
#define WIRE1_IT_HANDLER_2    SERCOM4_2_Handler
#define WIRE1_IT_HANDLER_3    SERCOM4_3_Handler

static const uint8_t SDA1 = PIN_WIRE1_SDA;
static const uint8_t SCL1 = PIN_WIRE1_SCL;
//----------------------------------------------

// USB
//----------------------------------------------
#define PIN_USB_HOST_ENABLE (29ul)
#define PIN_USB_DM          (30ul)
#define PIN_USB_DP          (31ul)
//----------------------------------------------

// I2S Interfaces
#define PIN_I2S_FS           (44u)
//----------------------------------------------
#define I2S_INTERFACES_COUNT 1

#define I2S_DEVICE           0
#define I2S_CLOCK_GENERATOR  3

#define PIN_I2S_SDO          (40u)
#define PIN_I2S_SDI          (41u)
#define PIN_I2S_SCK          (42u)
#define PIN_I2S_MCK          (43u)
#define PIN_I2S_FS           (44u)
//----------------------------------------------


#if !defined(VARIANT_QSPI_BAUD_DEFAULT)
  #define VARIANT_QSPI_BAUD_DEFAULT 5000000
#endif

#ifdef __cplusplus
}
#endif

//----------------------------------------------------------------------------
//        Arduino objects - C++ only
//----------------------------------------------------------------------------

#ifdef __cplusplus

//	------------------------
//	 SERCOM DEFINITION
//	------------------------
extern SERCOM sercom0; //SPI
extern SERCOM sercom1; // I2S occupies lines
extern SERCOM sercom2; //SPI1
extern SERCOM sercom3; //I2C 
extern SERCOM sercom4; //I2C1 or Serial2
extern SERCOM sercom5; //Serial1

extern Uart Serial1;

#endif
/*
* These serial port names are intended to allow libraries and architecture-neutral
* sketches to automatically default to the correct port name for a particular type
* of use.  For example, a GPS module would normally connect to SERIAL_PORT_HARDWARE_OPEN,
* the first hardware serial port whose RX/TX pins are not dedicated to another use.
*
* SERIAL_PORT_MONITOR        Port which normally prints to the Arduino Serial Monitor
*
* SERIAL_PORT_USBVIRTUAL     Port which is USB virtual serial
*
* SERIAL_PORT_LINUXBRIDGE    Port which connects to a Linux system via Bridge library
*
* SERIAL_PORT_HARDWARE       Hardware serial port, physical RX & TX pins.
*
* SERIAL_PORT_HARDWARE_OPEN  Hardware serial ports which are open for use.  Their RX & TX
*                            pins are NOT connected to anything by default.
*/
#define SERIAL_PORT_USBVIRTUAL      Serial
#define SERIAL_PORT_MONITOR         Serial
// Serial has no physical pins broken out, so it's not listed as HARDWARE port

#define SERIAL_PORT_HARDWARE        Serial1
#define SERIAL_PORT_HARDWARE_OPEN   Serial1

#endif // SAMD51 MicroMod Processor Board

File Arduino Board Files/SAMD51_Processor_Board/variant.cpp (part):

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  { PORTB, 13, PIO_DIGITAL,   PIN_ATTR_PWM_G, No_ADC_Channel, NOT_ON_PWM, TC4_CH1,      EXTERNAL_INT_13 }, // D9
  { PORTA, 14, PIO_DIGITAL,   PIN_ATTR_PWM_G, No_ADC_Channel, NOT_ON_PWM, NOT_ON_TIMER, EXTERNAL_INT_14 }, // D10
  { PORTA, 15, PIO_DIGITAL,   PIN_ATTR_PWM_G, No_ADC_Channel, NOT_ON_PWM, NOT_ON_TIMER, EXTERNAL_INT_15 }, // D12
  { PORTA, 18, PIO_DIGITAL,   PIN_ATTR_PWM_F, No_ADC_Channel, TCC1_CH2,   TC3_CH0,      EXTERNAL_INT_2 },  // D12 - I2C_INT
  { PORTA, 23, PIO_DIGITAL,   PIN_ATTR_PWM_G, No_ADC_Channel, TCC1_CH3,   TC2_CH1,      EXTERNAL_INT_13 }, // D13
  { PORTA, 19, PIO_DIGITAL,   PIN_ATTR_NONE,  No_ADC_Channel, NOT_ON_PWM, NOT_ON_TIMER, EXTERNAL_INT_3 },  // D14 - 3.3V_EN
  { PORTB, 22, PIO_DIGITAL,   PIN_ATTR_NONE,  No_ADC_Channel, NOT_ON_PWM, NOT_ON_TIMER, EXTERNAL_INT_6 },  // D15 - FLASH WP
  { PORTB, 23, PIO_DIGITAL,   PIN_ATTR_NONE,  No_ADC_Channel, NOT_ON_PWM, NOT_ON_TIMER, EXTERNAL_INT_7 },  // D16 - FLASH HOLD
  // ------------------------------------------------------------------------------------------------------------------------- 
  
  // Analog Pins 
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  // CAN BUS (CANRX/CANTX)
  // 38..39
  // ---------------------------------------------------------------------------------------------------------------------
  { PORTB, 14, PIO_AC_CLK, PIN_ATTR_PWM_F, No_ADC_Channel, TCC4_CH0, TC5_CH0, EXTERNAL_INT_14 },             // CAN TXO
  { PORTB, 15, PIO_AC_CLK, PIN_ATTR_PWM_F, No_ADC_Channel, TCC4_CH1, TC5_CH1, EXTERNAL_INT_15 },             // CAN RXI
  // ---------------------------------------------------------------------------------------------------------------------


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  // SPI (COPI, CIPO, SCK, CS)
  // 45....48
  // ---------------------------------------------------------------------------------------------------------------------
  { PORTA,  4, PIO_SERCOM_ALT, PIN_ATTR_DIGITAL, No_ADC_Channel, NOT_ON_PWM, NOT_ON_TIMER, EXTERNAL_INT_11 },// COPI
  { PORTA,  5, PIO_SERCOM_ALT, PIN_ATTR_DIGITAL, No_ADC_Channel, NOT_ON_PWM, NOT_ON_TIMER, EXTERNAL_INT_12 },// SCK
  { PORTA,  6, PIO_SERCOM_ALT, PIN_ATTR_DIGITAL, No_ADC_Channel, NOT_ON_PWM, NOT_ON_TIMER, EXTERNAL_INT_13 },// CIPO
  { PORTA,  7, PIO_SERCOM_ALT, PIN_ATTR_DIGITAL, No_ADC_Channel, NOT_ON_PWM, NOT_ON_TIMER, EXTERNAL_INT_13 },// CS
  // ---------------------------------------------------------------------------------------------------------------------

  // SPI1 (COPI1, CIPO1, SCK1, CS1)
  // 49....52
  // -----------------------------------------------------------------------------------------------------------------------
  { PORTA,  9,  PIO_SERCOM_ALT, PIN_ATTR_DIGITAL, No_ADC_Channel, NOT_ON_PWM, NOT_ON_TIMER, EXTERNAL_INT_1 },// COPI1 SER2.0
  { PORTA,  8,  PIO_SERCOM_ALT, PIN_ATTR_DIGITAL, No_ADC_Channel, NOT_ON_PWM, NOT_ON_TIMER, EXTERNAL_INT_0 },// SCK1  SER2.1
  { PORTA, 10,  PIO_SERCOM_ALT, PIN_ATTR_DIGITAL, No_ADC_Channel, NOT_ON_PWM, NOT_ON_TIMER, EXTERNAL_INT_2 },// CIPO1 SER2.2
  { PORTA, 11,  PIO_SERCOM_ALT, PIN_ATTR_DIGITAL, No_ADC_Channel, NOT_ON_PWM, NOT_ON_TIMER, EXTERNAL_INT_3 },// CS1   SER2.3
  // -----------------------------------------------------------------------------------------------------------------------
 
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

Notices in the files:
parts and their libraries:
SparkFun-Resistors: Licensing: Creative Commons ShareAlike 4.0 International - https://creativecommons.org/licenses/by-sa/4.0
SparkFun-Aesthetics: Released under the Creative Commons Attribution Share-Alike 4.0 License
SparkFun-Aesthetics: https://creativecommons.org/licenses/by-sa/4.0
